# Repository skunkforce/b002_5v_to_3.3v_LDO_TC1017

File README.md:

# edgy_board number b002
This design is part of the [edgy board project](https://github.com/skunkforce/edgy_boards). It provides a 3.3v LDO capable of 150ma using TC1017. 

# getting started
This repository uses submodules. After cloning use the command 

```$ git submodule update --init --recursive```

to pull the submodules before opening the project with kicad. 

# Tests
Tests can be found in [TESTS.md](TESTS.md)

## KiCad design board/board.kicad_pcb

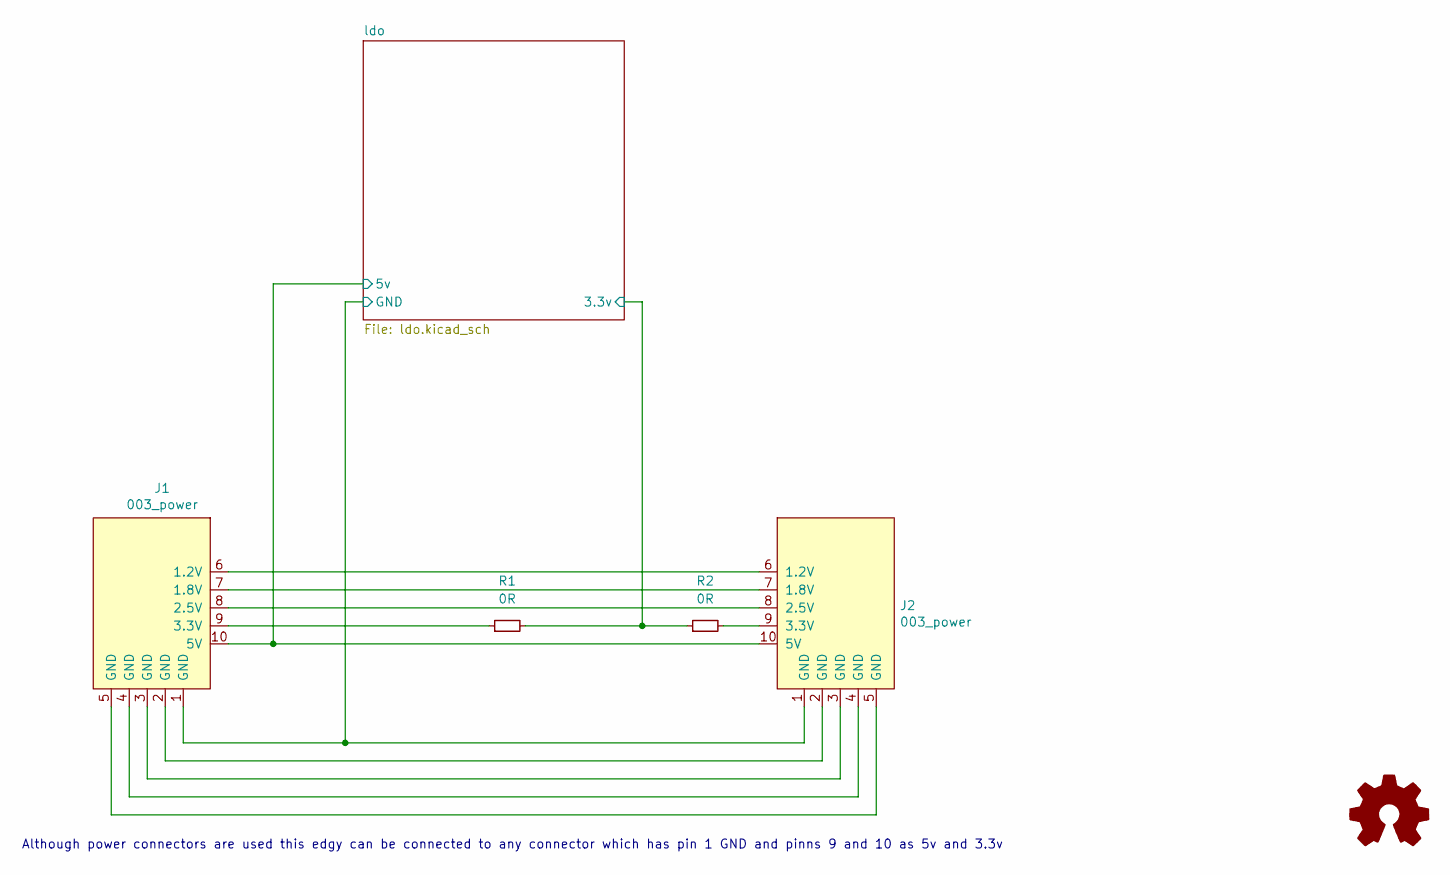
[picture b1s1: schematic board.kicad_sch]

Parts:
J1: 003_power; on_edge_2x05_device
J2: 003_power; on_edge_2x05_host
LOGO1: Logo_Open_Hardware_Small; OSHW-Symbol_6.7x6mm_SilkScreen
R1, R2: 0R; R_0603_1608Metric

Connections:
/ldo/3.3v: R1.2, R2.1; also elsewhere on the board
/ldo/5v: J1.10 (5V), J2.10 (5V); also elsewhere on the board
/ldo/GND: J1.1 (GND), J2.1 (GND); also elsewhere on the board
unnamed: J1.2 (GND), J2.2 (GND)
unnamed: J1.3 (GND), J2.3 (GND)
unnamed: J1.4 (GND), J2.4 (GND)
unnamed: J1.5 (GND), J2.5 (GND)
unnamed: J1.6 (1.2V), J2.6 (1.2V)
unnamed: J1.7 (1.8V), J2.7 (1.8V)
unnamed: J1.8 (2.5V), J2.8 (2.5V)
unnamed: J1.9 (3.3V), R1.1
unnamed: J2.9 (3.3V), R2.2

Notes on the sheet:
Although power connectors are used this edgy can be connected to any connector which has pin 1 GND and pinns 9 and 10 as 5v and 3.3v

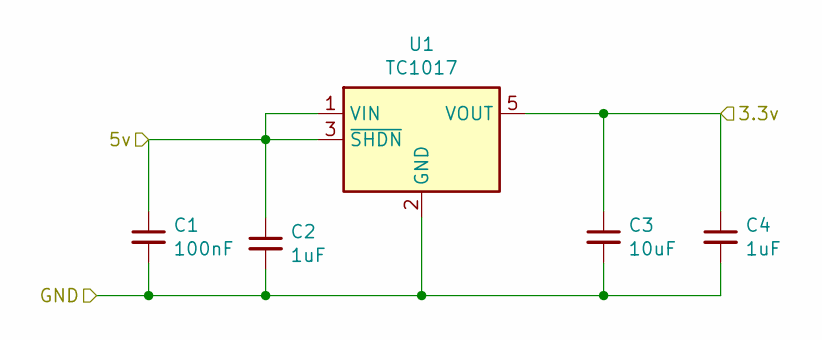
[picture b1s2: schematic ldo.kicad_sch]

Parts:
C1: 100nF; C_0603_1608Metric
C2, C4: 1uF; C_0603_1608Metric
C3: 10uF; C_0603_1608Metric
U1: TC1017; SOT-23-5; MPN TC1017-3.3VCTTR; Digi-Key_PN TC1017-3.3VCTCT-ND

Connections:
/ldo/3.3v: C3.1, C4.1, U1.5 (VOUT); also elsewhere on the board
/ldo/5v: C1.1, C2.1, U1.1 (VIN), U1.3 (~SHDN); also elsewhere on the board
/ldo/GND: C1.2, C2.2, C3.2, C4.2, U1.2 (GND); also elsewhere on the board

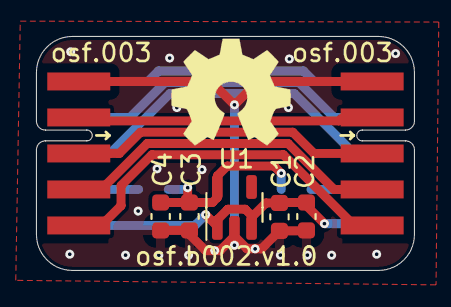
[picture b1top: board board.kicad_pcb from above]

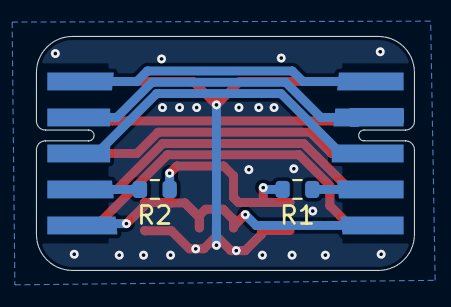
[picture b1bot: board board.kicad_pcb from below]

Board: 2 copper layers, 21.0 x 13.0 mm, 10 parts (2 on the bottom side), 12 nets.

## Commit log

2023-02-28 initial
2023-02-28 initial README
2023-03-01 updated put_on_edge submodule
2023-03-29 added pours, silkscreen names and updated put_on_edge
